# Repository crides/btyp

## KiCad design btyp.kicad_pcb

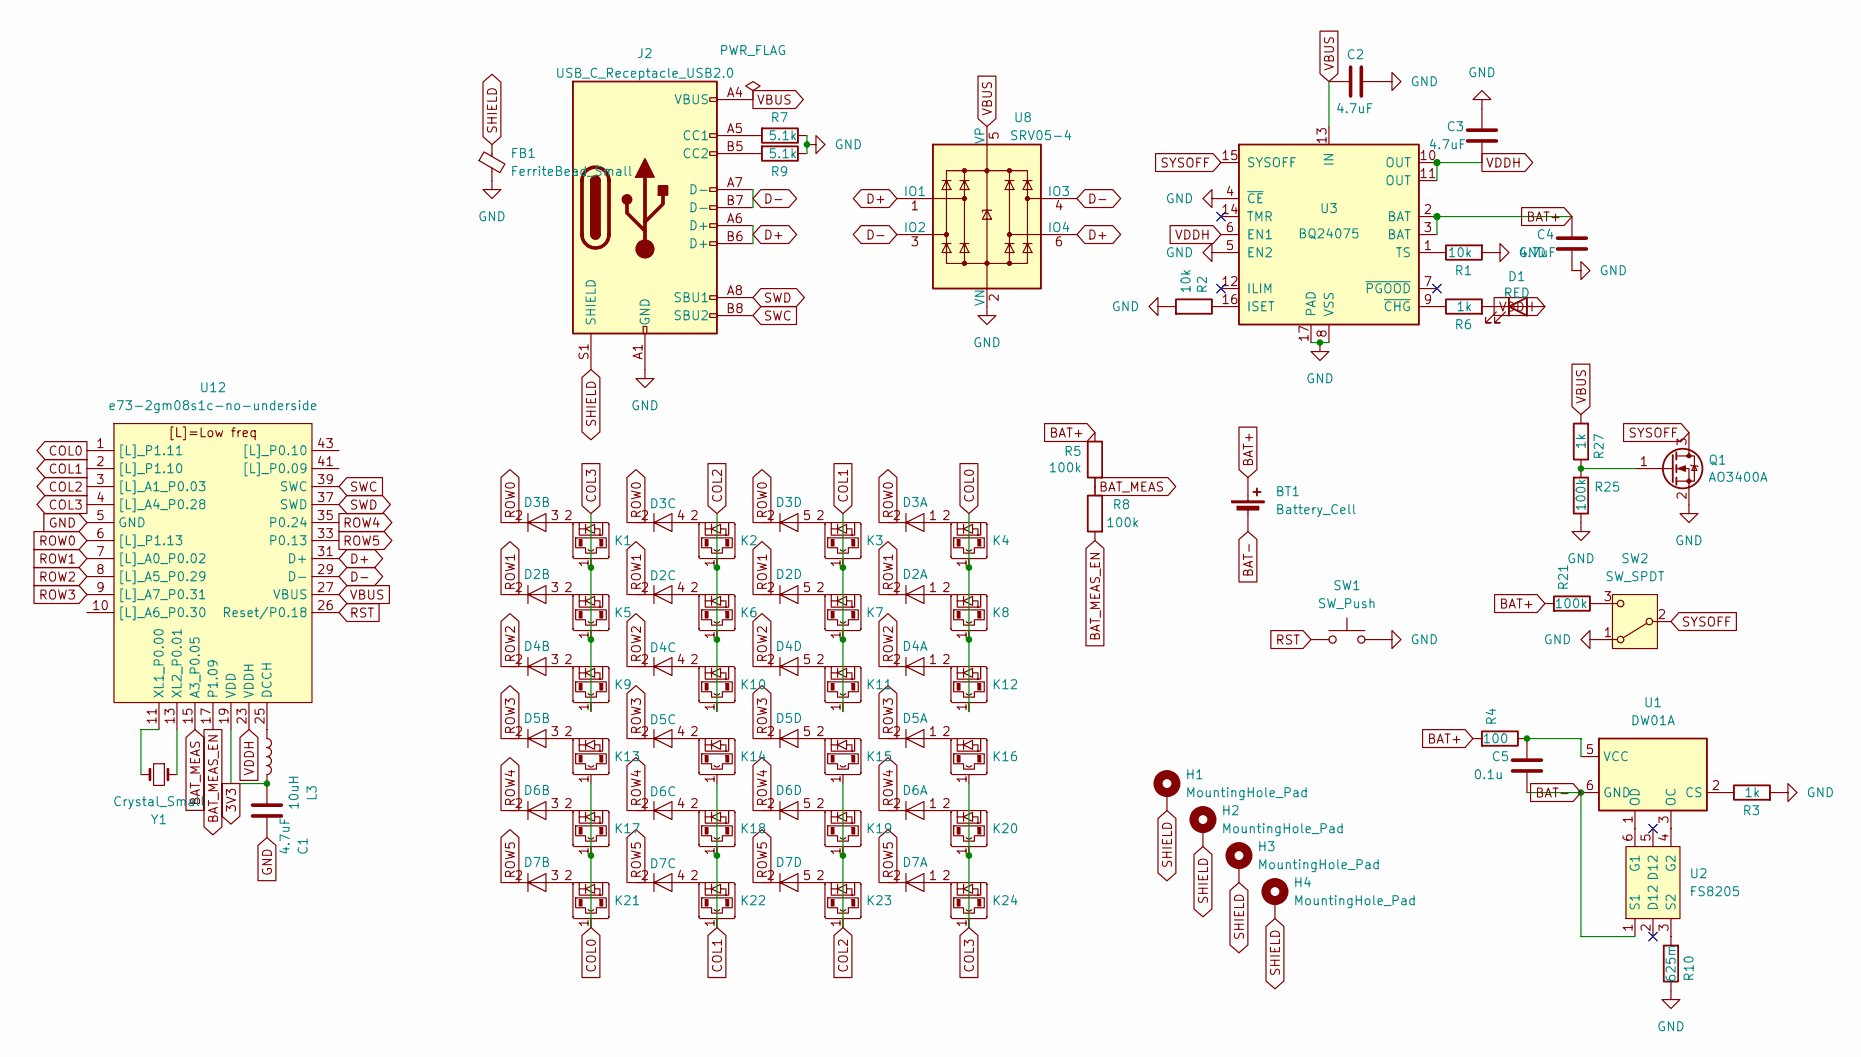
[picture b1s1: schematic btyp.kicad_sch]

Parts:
BT1: Battery_Cell; RJD2032C1ST1
C1, C2, C3, C4: 4.7uF; C_0603_1608Metric
C5: 0.1u; C_0603_1608Metric
D1: RED; LED_0805_2012Metric
D2, D3, D4, D5, D6, D7: SOT-23-5
FB1: FerriteBead_Small; L_1206_3216Metric
H1, H2, H3, H4: MountingHole_Pad; M2
J2: USB_C_Receptacle_USB2.0; USB_C_Receptacle_HRO_TYPE-C-31-M-12
K1, K2, K3, K4, K5, K6, K7, K8, K9, K10, K11, K12, K13, K14, K15, K16, K17, K18, K19, K20, K21, K22, K23, K24: diode-choc; PG1316M
L3: 10uH; L_0603_1608Metric
Q1: AO3400A; SOT-23
R1, R2: 10k; R_0603_1608Metric
R3, R6, R27: 1k; R_0603_1608Metric
R4: 100; R_0603_1608Metric
R5, R8, R21, R25: 100k; R_0603_1608Metric
R7, R9: 5.1k; R_0603_1608Metric
R10: 625m; R_0603_1608Metric
SW1: SW_Push; SW_SPST_EVQP7C
SW2: SW_SPDT; SW_SPDT_PCM12
U1: DW01A; SOT-23-6
U2: FS8205; SOT-23-6; LCSC C32254
U3: BQ24075; VQFN-16-1EP_3x3mm_P0.5mm_EP1.68x1.68mm_ThermalVias
U8: SRV05-4; SOT-23-6
U12: e73-2gm08s1c-no-underside; e73-2g4m08s1c-no-underside
Y1: Crystal_Small; Crystal_SMD_MicroCrystal_CM9V-T1A-2Pin_1.6x1.0mm

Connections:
3V3: C1.1, L3.2, U12.19 (VDD)
BAT+: BT1.1 (+), C4.1, R4.2, R5.1, R21.2, U3.2 (BAT), U3.3 (BAT)
BAT-: BT1.2 (-), C5.2, U1.6 (GND), U2.1 (S1)
BAT_MEAS: R5.2, R8.1, U12.15 (A3_P0.05)
BAT_MEAS_EN: R8.2, U12.17 (P1.09)
COL0: K4.1, K8.1, K12.1, K13.1, K17.1, K21.1, U12.1 ([L]_P1.11)
COL1: K3.1, K7.1, K11.1, K14.1, K18.1, K22.1, U12.2 ([L]_P1.10)
COL2: K2.1, K6.1, K10.1, K15.1, K19.1, K23.1, U12.3 ([L]_A1_P0.03)
COL3: K1.1, K5.1, K9.1, K16.1, K20.1, K24.1, U12.4 ([L]_A4_P0.28)
D+: J2.A6 (D+), J2.B6 (D+), U8.1 (IO1), U8.6 (IO4), U12.31 (D+)
D-: J2.A7 (D-), J2.B7 (D-), U8.3 (IO2), U8.4 (IO3), U12.29 (D-)
GND: C1.2, C2.2, C3.1, C4.2, FB1.2, J2.A1 (GND), J2.A12 (GND), J2.B1 (GND), J2.B12 (GND), Q1.2 (S), R1.2, R2.2, R3.2, R7.1, R9.1, R10.1, R25.1, SW1.2, SW2.1 (A), U3.4 (~CE), U3.5 (EN2), U3.8 (VSS), U3.17 (PAD), U8.2 (VN), U12.5 (GND), U12.21 (GND), U12.24 (GND)
unnamed: D1.1 (K), R6.2
unnamed: D2.1 (A), K8.2
unnamed: D2.3 (A), K5.2
unnamed: D2.4 (A), K6.2
unnamed: D2.5 (A), K7.2
unnamed: D3.1 (A), K4.2
unnamed: D3.3 (A), K1.2
unnamed: D3.4 (A), K2.2
unnamed: D3.5 (A), K3.2
unnamed: D4.1 (A), K12.2
unnamed: D4.3 (A), K9.2
unnamed: D4.4 (A), K10.2
unnamed: D4.5 (A), K11.2
unnamed: D5.1 (A), K16.2
unnamed: D5.3 (A), K13.2
unnamed: D5.4 (A), K14.2
unnamed: D5.5 (A), K15.2
unnamed: D6.1 (A), K20.2
unnamed: D6.3 (A), K17.2
unnamed: D6.4 (A), K18.2
unnamed: D6.5 (A), K19.2
unnamed: D7.1 (A), K24.2
unnamed: D7.3 (A), K21.2
unnamed: D7.4 (A), K22.2
unnamed: D7.5 (A), K23.2
unnamed: J2.A5 (CC1), R7.2
unnamed: J2.B5 (CC2), R9.2
unnamed: Q1.1 (G), R25.2, R27.1
unnamed: R21.1, SW2.3 (C)
unnamed: R3.1, U1.2 (CS)
unnamed: U1.3 (OC), U2.4 (G2)
unnamed: U1.1 (OD), U2.6 (G1)
unnamed: C5.1, R4.1, U1.5 (VCC)
unnamed: R10.2, U2.3 (S2)
unnamed: R2.1, U3.16 (ISET)
unnamed: R1.1, U3.1 (TS)
unnamed: R6.1, U3.9 (~CHG)
unnamed: L3.1, U12.25 (DCCH)
unnamed: U12.11 (XL1_P0.00), Y1.2
unnamed: U12.13 (XL2_P0.01), Y1.1
ROW0: D3.2 (K), U12.6 ([L]_P1.13)
ROW1: D2.2 (K), U12.7 ([L]_A0_P0.02)
ROW2: D4.2 (K), U12.8 ([L]_A5_P0.29)
ROW3: D5.2 (K), U12.9 ([L]_A7_P0.31)
ROW4: D6.2 (K), U12.35 (P0.24)
ROW5: D7.2 (K), U12.33 (P0.13)
RST: SW1.1, U12.26 (Reset/P0.18)
SHIELD: FB1.1, H1.1, H2.1, H3.1, H4.1, J2.S1 (SHIELD)
SWC: J2.B8 (SBU2), U12.39 (SWC)
SWD: J2.A8 (SBU1), U12.37 (SWD)
SYSOFF: Q1.3 (D), SW2.2 (B), U3.15 (SYSOFF)
VBUS: C2.1, J2.A4 (VBUS), J2.A9 (VBUS), J2.B4 (VBUS), J2.B9 (VBUS), R27.2, U3.13 (IN), U8.5 (VP), U12.27 (VBUS)
VDDH: C3.2, D1.2 (A), U3.6 (EN1), U3.10 (OUT), U3.11 (OUT), U12.23 (VDDH)

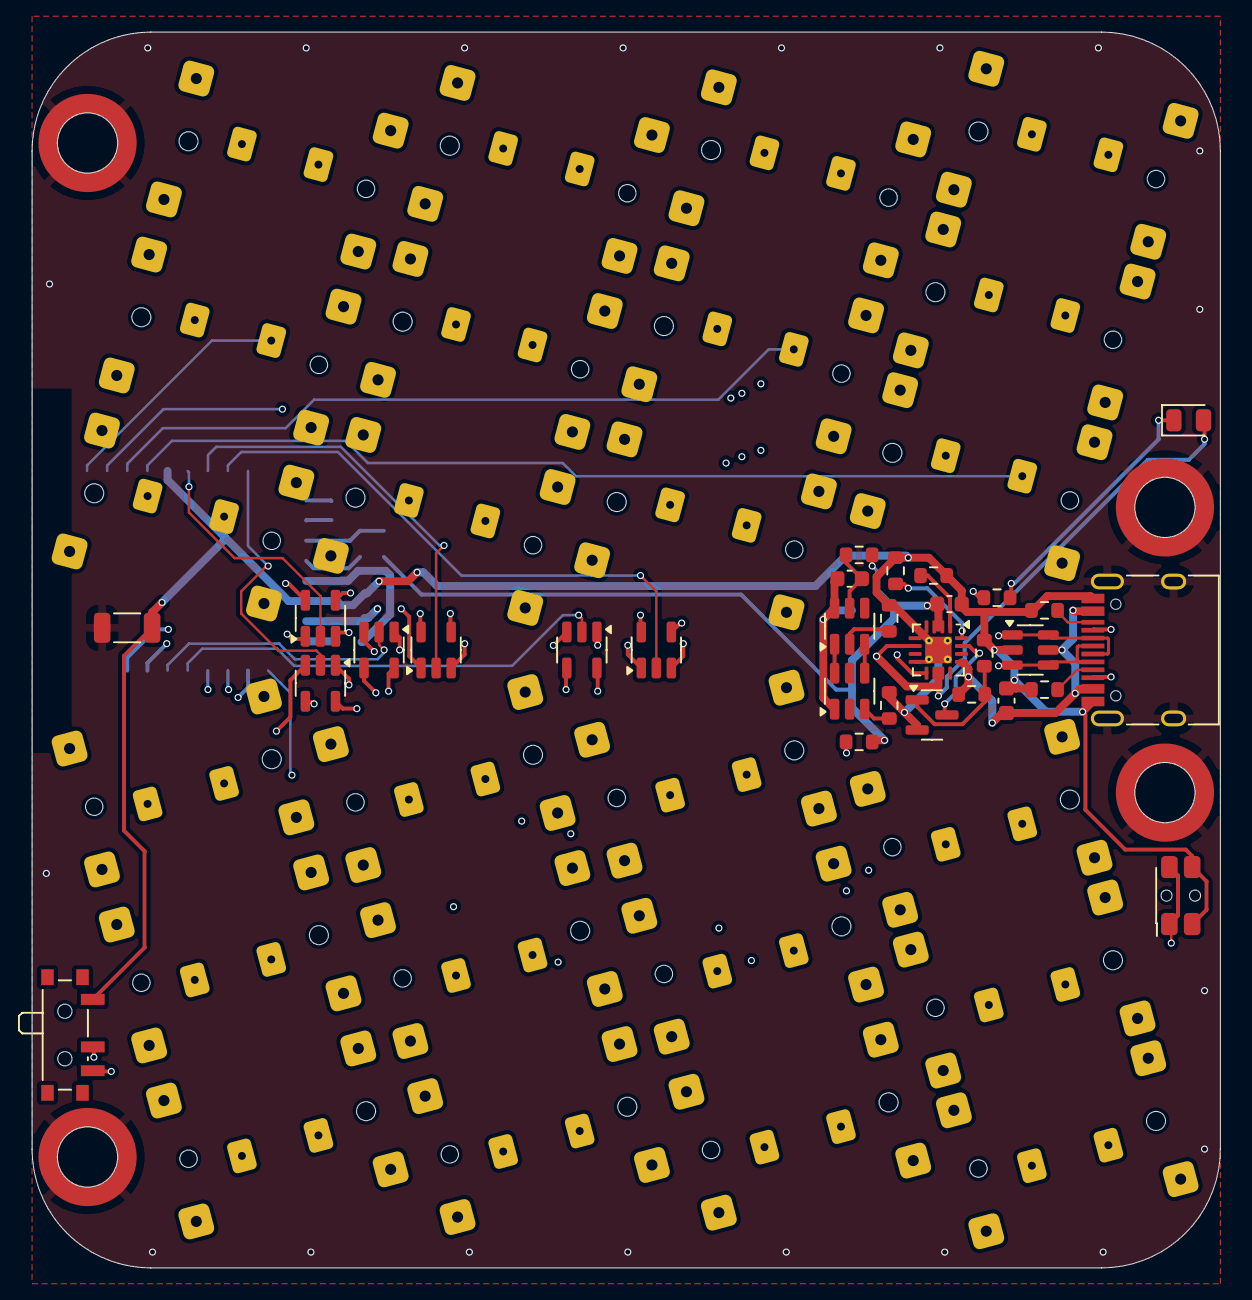
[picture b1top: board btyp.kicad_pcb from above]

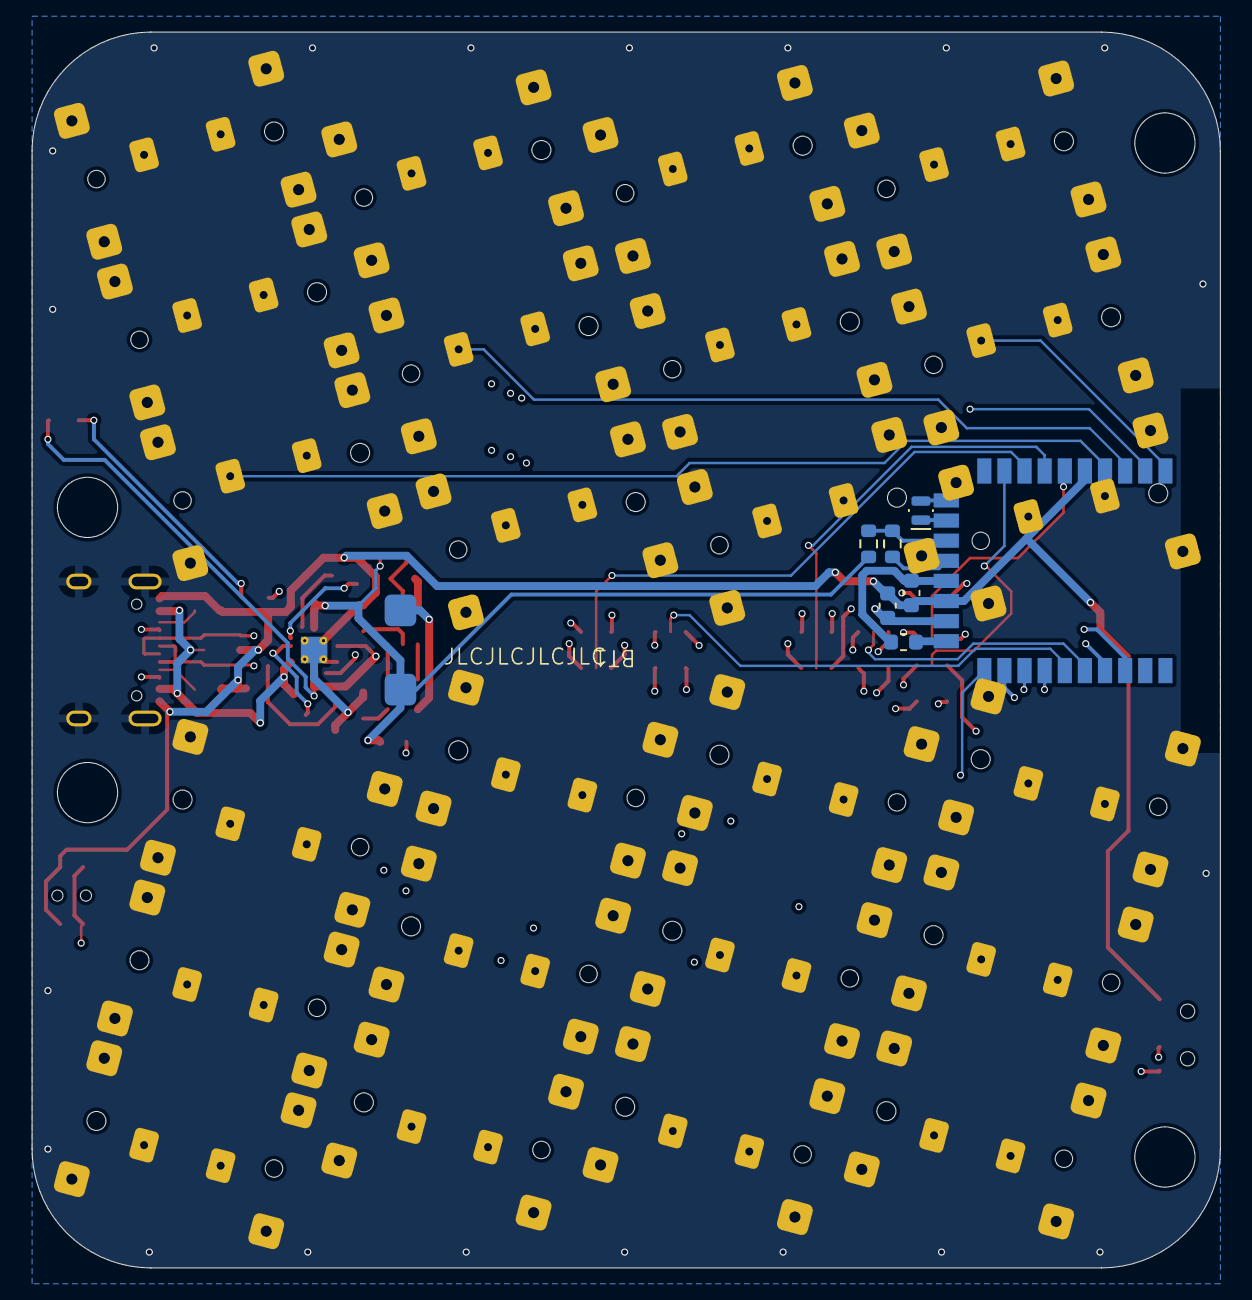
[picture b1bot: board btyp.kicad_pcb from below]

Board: 4 copper layers, 75.0 x 78.0 mm, 66 parts (8 on the bottom side), 65 nets.
